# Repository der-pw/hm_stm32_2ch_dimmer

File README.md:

# hm_stm32_2ch_dimmer

Platinendesign für einen Asksin++ 2 Kanaldimmer, der mit einem STM32 angetrieben wird.
Basiert auf der guten Vorarbeit von pa-pa und seinem STM32 Dimmer https://github.com/pa-pa/STM32Dimmer

top

bottom

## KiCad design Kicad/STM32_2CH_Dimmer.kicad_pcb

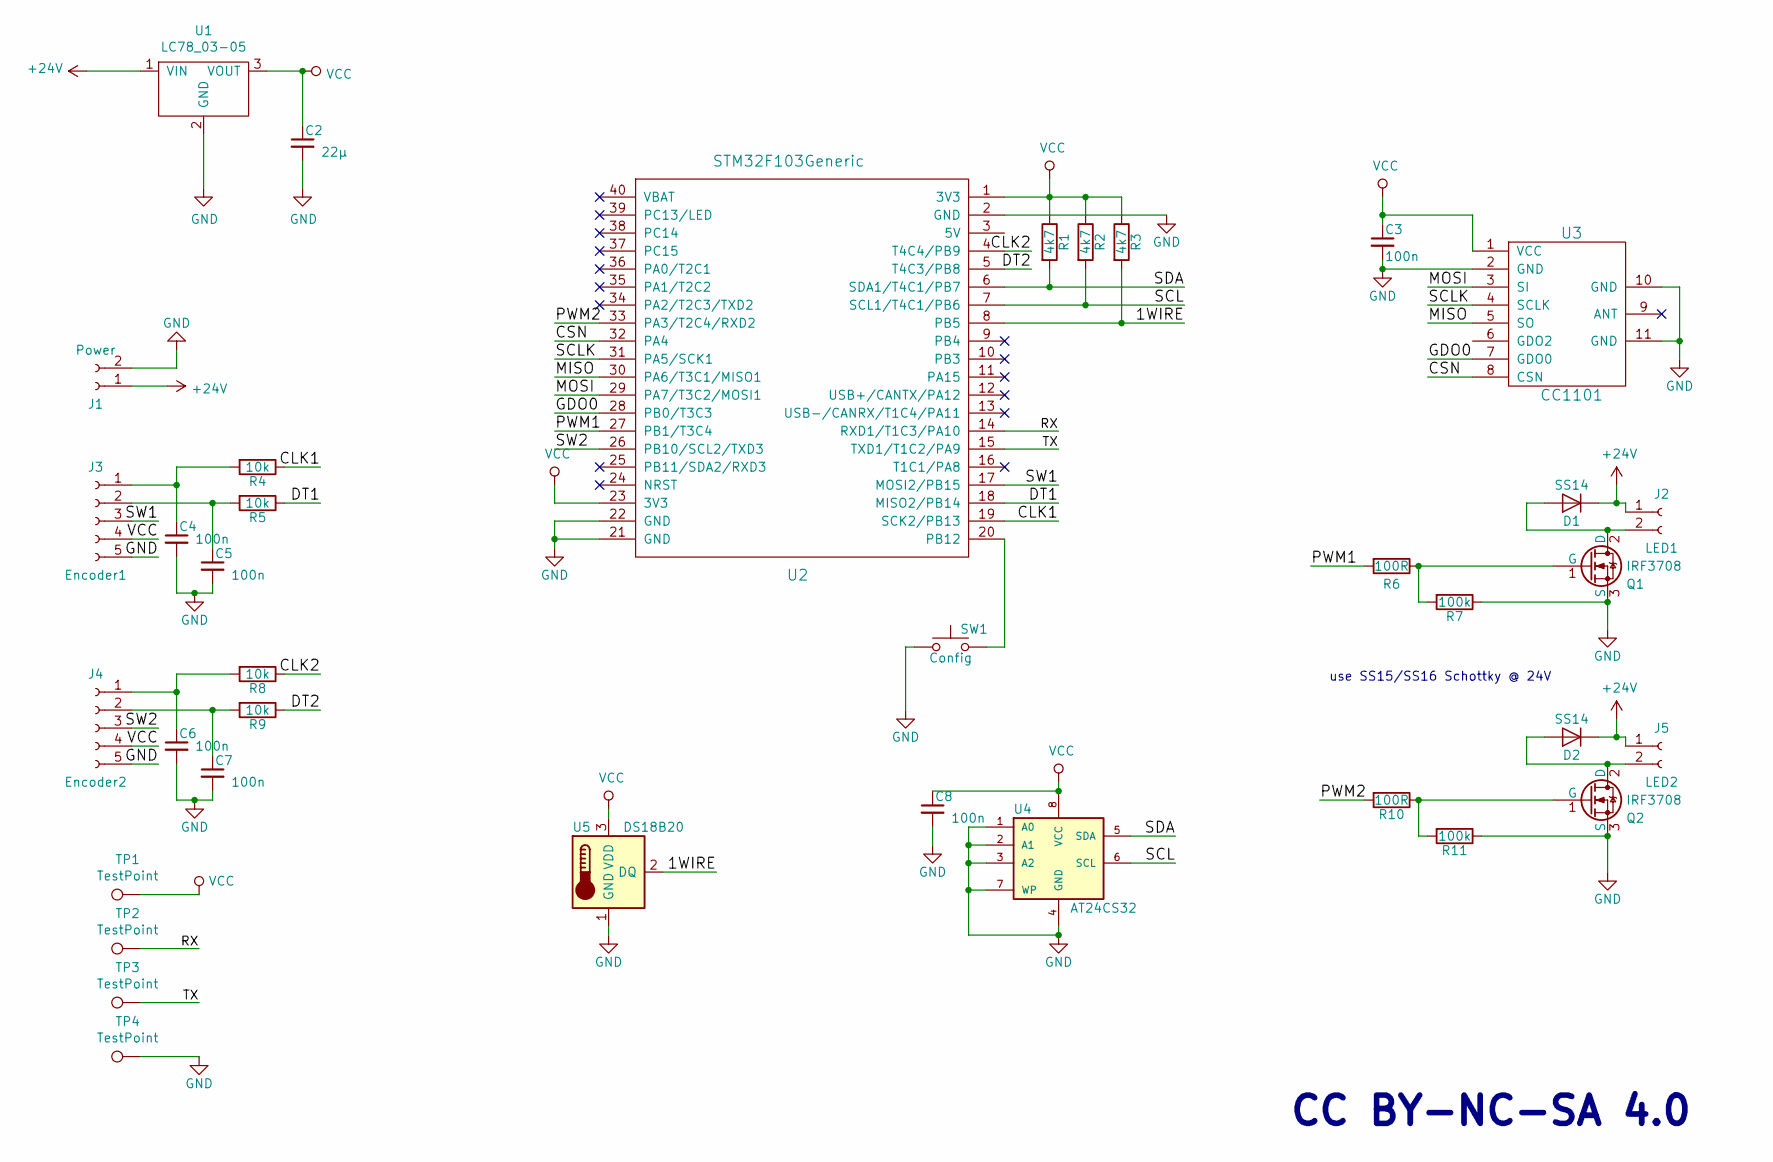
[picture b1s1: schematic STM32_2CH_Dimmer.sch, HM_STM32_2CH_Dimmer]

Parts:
C2: 22µ; C_0805_2012Metric_Pad1.15x1.40mm_HandSolder
C3, C4, C5, C6, C7, C8: 100n; C_0805_2012Metric_Pad1.15x1.40mm_HandSolder
D1, D2: SS14; D_SMA
J1: Power; TerminalBlock_bornier-2_P5.08mm
J2: LED1; TerminalBlock_bornier-2_P5.08mm
J3: Encoder1; Pin_Header_Straight_1x05_Pitch2.54mm
J4: Encoder2; Pin_Header_Straight_1x05_Pitch2.54mm
J5: LED2; TerminalBlock_bornier-2_P5.08mm
Q1, Q2: IRF3708; TO-220-3_Vertical
R1, R2, R3: 4k7; R_0805_2012Metric_Pad1.15x1.40mm_HandSolder
R4, R5, R8, R9: 10k; R_0805_2012Metric_Pad1.15x1.40mm_HandSolder
R6, R10: 100R; R_0805_2012Metric_Pad1.15x1.40mm_HandSolder
R7, R11: 100k; R_0805_2012Metric_Pad1.15x1.40mm_HandSolder
SW1: Config; SW_PUSH_6mm_H4.3mm
TP1, TP2, TP3, TP4: TestPoint; TestPoint_Pad_D1.5mm
U1: LC78_03-05
U2: STM32F103Generic
U3: CC1101; CC1101_Module
U4: AT24CS32; SOIC-8_3.9x4.9mm_Pitch1.27mm
U5: DS18B20; TO-92_Inline_Narrow_Oval

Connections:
+24V: D1.1 (K), D2.1 (K), J1.1, J2.1, J5.1, U1.1 (VIN)
/1WIRE: R3.2, U2.8 (PB5), U5.2 (DQ)
/CLK1: R4.1, U2.19 (SCK2/PB13)
/CLK2: R8.1, U2.4 (T4C4/PB9)
/CSN: U2.32 (PA4), U3.8 (CSN)
/DT1: R5.1, U2.18 (MISO2/PB14)
/DT2: R9.1, U2.5 (T4C3/PB8)
/GDO0: U2.28 (PB0/T3C3), U3.7 (GDO0)
/MISO: U2.30 (PA6/T3C1/MISO1), U3.5 (SO)
/MOSI: U2.29 (PA7/T3C2/MOSI1), U3.3 (SI)
/PWM1: R6.2, U2.27 (PB1/T3C4)
/PWM2: R10.2, U2.33 (PA3/T2C4/RXD2)
/RX: TP2.1, U2.14 (RXD1/T1C3/PA10)
/SCL: R2.2, U2.7 (SCL1/T4C1/PB6), U4.6 (SCL)
/SCLK: U2.31 (PA5/SCK1), U3.4 (SCLK)
/SDA: R1.2, U2.6 (SDA1/T4C1/PB7), U4.5 (SDA)
/SW1: J3.3, U2.17 (MOSI2/PB15)
/SW2: J4.3, U2.26 (PB10/SCL2/TXD3)
/TX: TP3.1, U2.15 (TXD1/T1C2/PA9)
GND: C2.2, C3.2, C4.2, C5.2, C6.2, C7.2, C8.2, J1.2, J3.5, J4.5, Q1.3 (S), Q2.3 (S), R7.1, R11.1, SW1.1, TP4.1, U1.2 (GND), U2.2 (GND), U2.21 (GND), U2.22 (GND), U3.2 (GND), U3.10 (GND), U3.11 (GND), U4.1 (A0), U4.2 (A1), U4.3 (A2), U4.4 (GND), U4.7 (WP), U5.1 (GND)
unnamed: C4.1, J3.1, R4.2
unnamed: C5.1, J3.2, R5.2
unnamed: C6.1, J4.1, R8.2
unnamed: C7.1, J4.2, R9.2
unnamed: D1.2 (A), J2.2, Q1.2 (D)
unnamed: D2.2 (A), J5.2, Q2.2 (D)
unnamed: Q1.1 (G), R6.1, R7.2
unnamed: Q2.1 (G), R10.1, R11.2
unnamed: SW1.2, U2.20 (PB12)
VCC: C2.1, C3.1, C8.1, J3.4, J4.4, R1.1, R2.1, R3.1, TP1.1, U1.3 (VOUT), U2.1 (3V3), U2.23 (3V3), U3.1 (VCC), U4.8 (VCC), U5.3 (VDD)

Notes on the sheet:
CC BY-NC-SA 4.0
use SS15/SS16 Schottky @ 24V

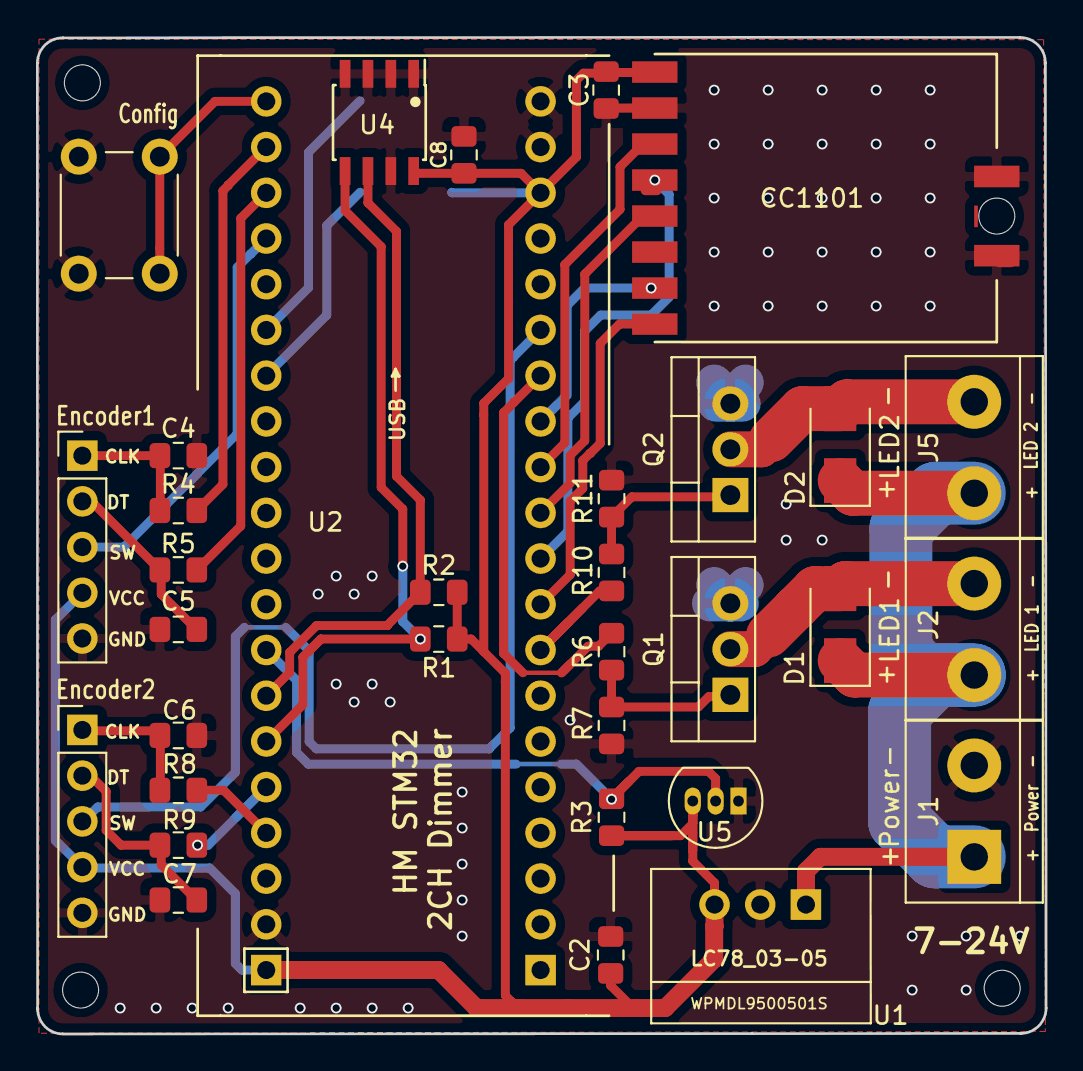
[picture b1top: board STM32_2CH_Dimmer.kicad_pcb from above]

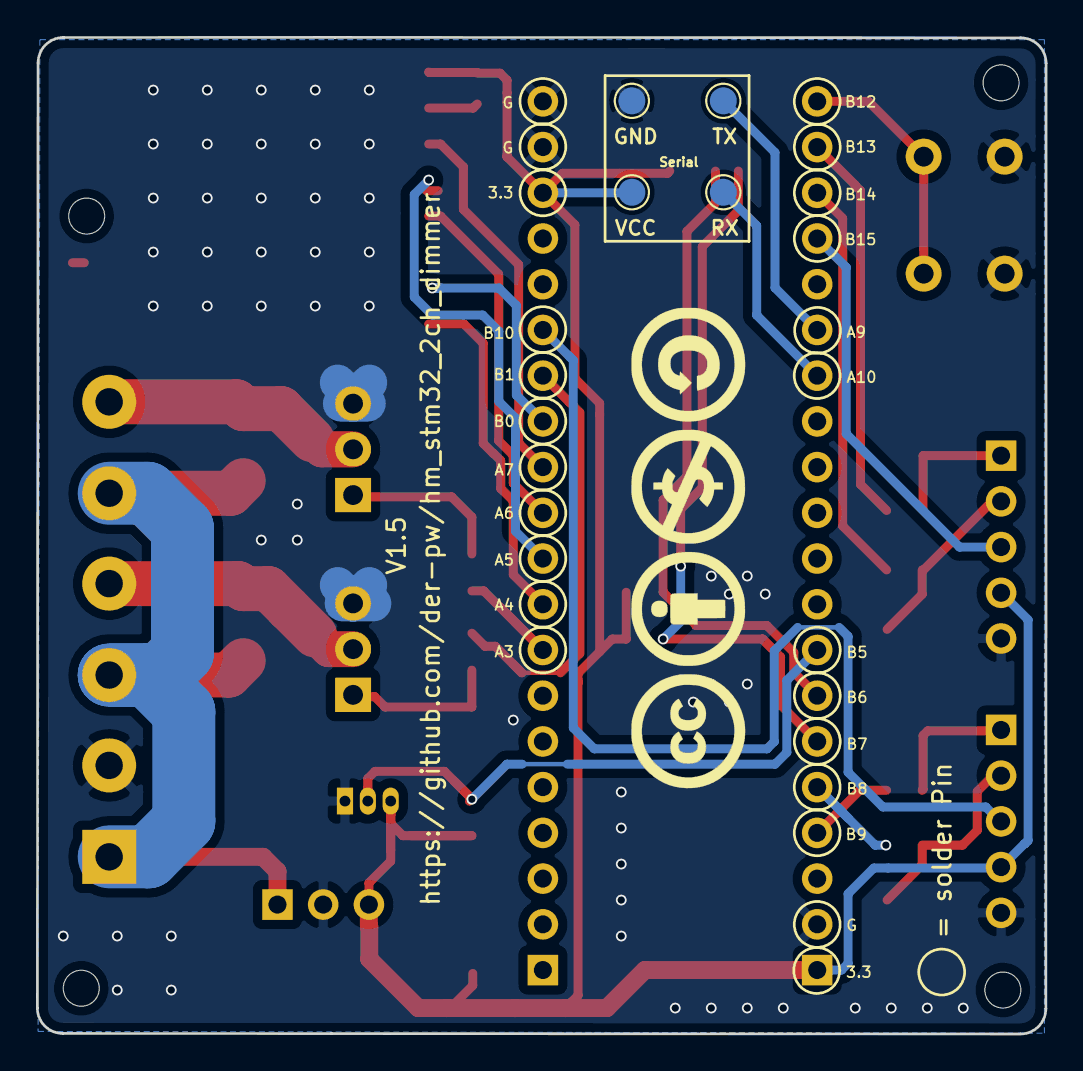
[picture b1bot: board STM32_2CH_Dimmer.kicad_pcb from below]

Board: 2 copper layers, 56.0 x 55.4 mm, 37 parts (4 on the bottom side), 30 nets.

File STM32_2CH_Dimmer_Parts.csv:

Reference, Quantity, Value, Footprint, Datasheet
C2 ,1,"22µ","Capacitor_SMD:C_0805_2012Metric_Pad1.15x1.40mm_HandSolder",""
C3 C8 C7 C6 C5 C4 ,6,"100n","Capacitor_SMD:C_0805_2012Metric_Pad1.15x1.40mm_HandSolder",""
D1 D2 ,2,"SS14","Diodes_SMD:D_SMA","https://de.aliexpress.com/item/100PCS-SMA-Rectifier-diode-1N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"
J1 ,1,"Power","Terminal_Blocks:TerminalBlock_bornier-2_P5.08mm","~"
J2 ,1,"LED1","Terminal_Blocks:TerminalBlock_bornier-2_P5.08mm","~"
J3 ,1,"Encoder1","Pin_Headers:Pin_Header_Straight_1x05_Pitch2.54mm","~"
J4 ,1,"Encoder2","Pin_Headers:Pin_Header_Straight_1x05_Pitch2.54mm","~"
J5 ,1,"LED2","Terminal_Blocks:TerminalBlock_bornier-2_P5.08mm","~"
Q1 Q2 ,2,"IRF3708","Package_TO_SOT_THT:TO-220-3_Vertical",""
R1 R2 R3 ,3,"4k7","Resistor_SMD:R_0805_2012Metric_Pad1.15x1.40mm_HandSolder",""
R6 R10 ,2,"100R","Resistor_SMD:R_0805_2012Metric_Pad1.15x1.40mm_HandSolder",""
R7 R11 ,2,"100k","Resistor_SMD:R_0805_2012Metric_Pad1.15x1.40mm_HandSolder",""
R8 R9 R4 R5 ,4,"10k","Resistor_SMD:R_0805_2012Metric_Pad1.15x1.40mm_HandSolder",""
SW1 ,1,"Config","Button_Switch_THT:SW_PUSH_6mm_H4.3mm","https://de.aliexpress.com/item/100PCS-LOT-3-4-2MM-Micro-butt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"
TP1 TP2 TP3 TP4 ,4,"TestPoint","TestPoint:TestPoint_Pad_D1.5mm","~"
U1 ,1,"LC78_03-05","Homebrew:LC78_03-05","https://www.reichelt.de/dc-dc-wandler-1-65-w-3-3-v-500-ma-to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"
U2 ,1,"STM32F103Generic","Homebrew:STM32F103Generic","https://de.aliexpress.com/item/STM32F103CBT6-Maple-Mini-ARM-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"
U3 ,1,"CC1101","Homebrew:CC1101_Module","https://de.aliexpress.com/item/CC1101-Wireless-Module-Long-D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"
U4 ,1,"AT24CS32","Housings_SOIC:SOIC-8_3.9x4.9mm_Pitch1.27mm","https://de.aliexpress.com/item/20PCS-24c32-AT24c32-SOP8-AT24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"
U5 ,1,"DS18B20","TO_SOT_Packages_THT:TO-92_Inline_Narrow_Oval","https://de.aliexpress.com/item/DS18B20-18B20-Programmable-Re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"

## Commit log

2019-09-29 some fixes
2019-10-20 V1.1
2019-11-04 V1.2
2019-11-04 Gerber export
2019-11-04 part csv
2019-11-08 V1.3
    minor fixes
    add test pads for serial connection
2019-11-09 info C1
2019-11-15 update 1.4 final
2019-12-28 Update V1.5
    add missing Via at R3
2019-12-30 Gehäuse
2020-10-05 cleanup und create gerber.zip
2021-03-23 Update README.md
    End of "WOP" its stable now
